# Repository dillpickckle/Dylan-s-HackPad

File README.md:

# Dylan-s-HackPad

This project is a custom 3×3 macro pad built around the Seeed XIAO RP2040, featuring a diode-protected key matrix, a rotary encoder for dynamic input, and a 128×32 SSD1306 OLED for real-time status display (RN it displays larry the SLUG). The design uses a proper row/column matrix to prevent ghosting and is powered by QMK firmware for full remapping, layers, and encoder support. This is my first time working with KiCad, and I was excited to learn how to use it through this project. It also helped to sharpen my Fusion 360 and coding skills, and that's why I made this project. 

Schematic: 

PCB:

CAD IMAGE: 

 BOM: 
9x Cherry MX Switches

9x DSA Keycaps

4x M3x5x4 Heatset inserts

9x 1N4148 DO-35 Diodes.

1x 0.91" 128x32 OLED Display

1x EC11 Rotary Encoder

1x XIAO RP2040

1x Case (2 3d Printed parts)

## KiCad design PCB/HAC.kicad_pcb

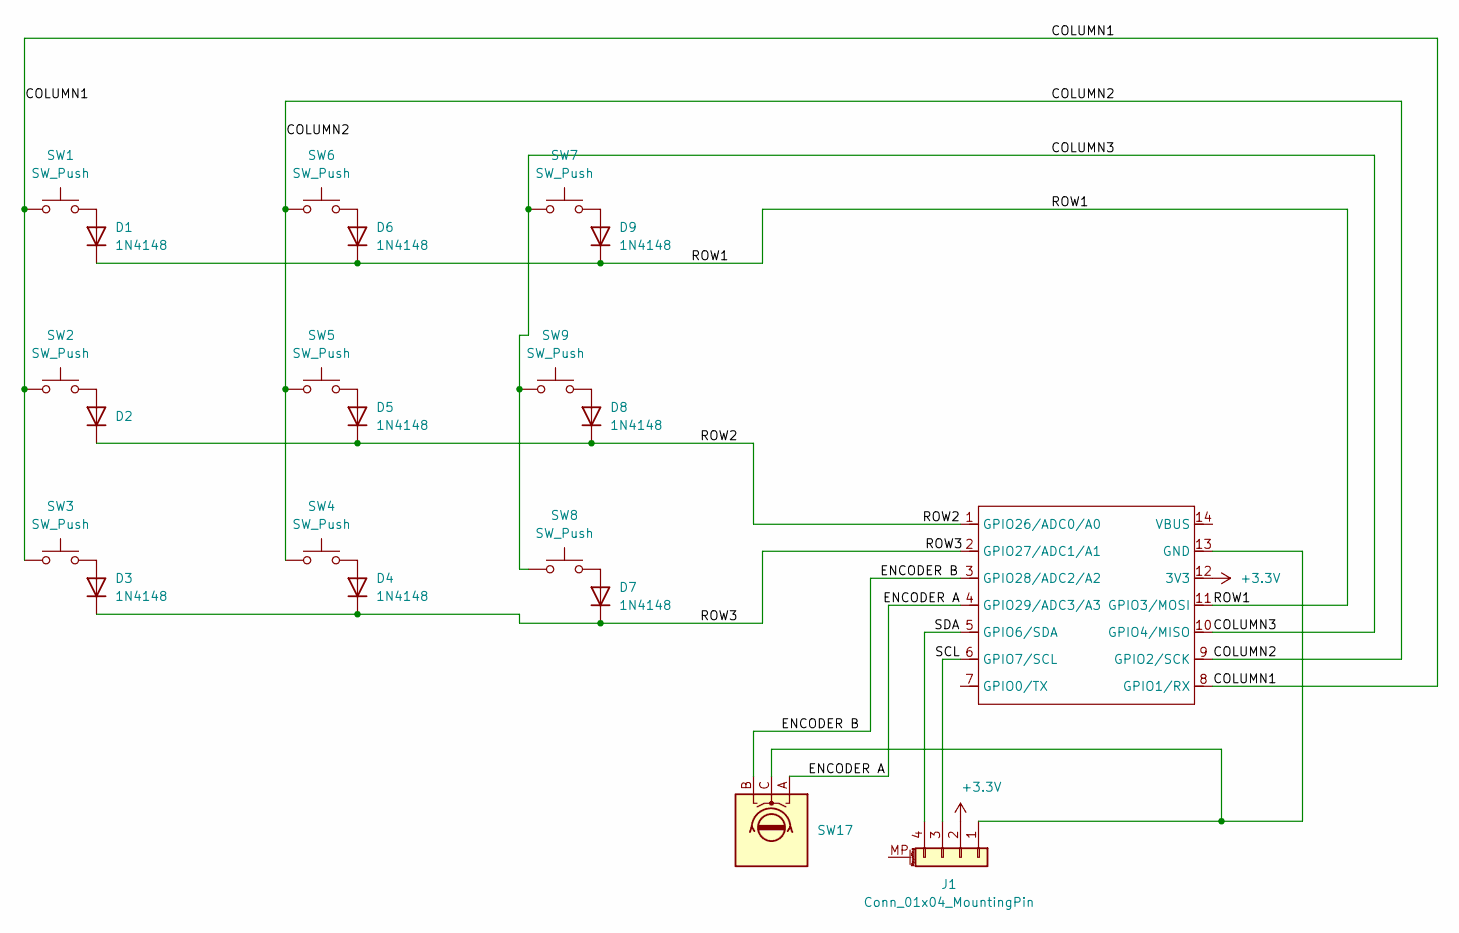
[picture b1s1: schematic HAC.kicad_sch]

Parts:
D1, D2, D3, D4, D5, D6, D7, D8, D9: 1N4148; D_DO-35_SOD27_P7.62mm_Horizontal
J1: Conn_01x04_MountingPin; SSD1306-0.91-OLED-4pin-128x32 (1)
SW1, SW2, SW3, SW4, SW5, SW6, SW7, SW8, SW9: SW_Push; SW_Cherry_MX_1.00u_PCB
SW17: RotaryEncoder; RotaryEncoder_Alps_EC11E_Vertical_H20mm
U1: XIAO-RP2040-DIP

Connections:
+3.3V: J1.2 (VCC), U1.12 (3V3)
/COLUMN1: SW1.1, SW2.1, SW3.1, U1.8 (GPIO1/RX)
/COLUMN2: SW4.1, SW5.1, SW6.1, U1.9 (GPIO2/SCK)
/COLUMN3: SW7.1, SW8.1, SW9.1, U1.10 (GPIO4/MISO)
/ENCODER A: SW17.A, U1.4 (GPIO29/ADC3/A3)
/ENCODER B: SW17.B, U1.3 (GPIO28/ADC2/A2)
/ROW1: D1.1 (K), D6.1 (K), D9.1 (K), U1.11 (GPIO3/MOSI)
/ROW2: D2.1 (K), D5.1 (K), D8.1 (K), U1.1 (GPIO26/ADC0/A0)
/ROW3: D3.1 (K), D4.1 (K), D7.1 (K), U1.2 (GPIO27/ADC1/A1)
/SCL: J1.3 (SCL), U1.6 (GPIO7/SCL)
/SDA: J1.4 (SDA), U1.5 (GPIO6/SDA)
unnamed: D1.2 (A), SW1.2
unnamed: D2.2 (A), SW2.2
unnamed: D3.2 (A), SW3.2
unnamed: D4.2 (A), SW4.2
unnamed: D5.2 (A), SW5.2
unnamed: D6.2 (A), SW6.2
unnamed: D7.2 (A), SW8.2
unnamed: D8.2 (A), SW9.2
unnamed: D9.2 (A), SW7.2
unnamed: J1.1 (GND), SW17.C, U1.13 (GND)

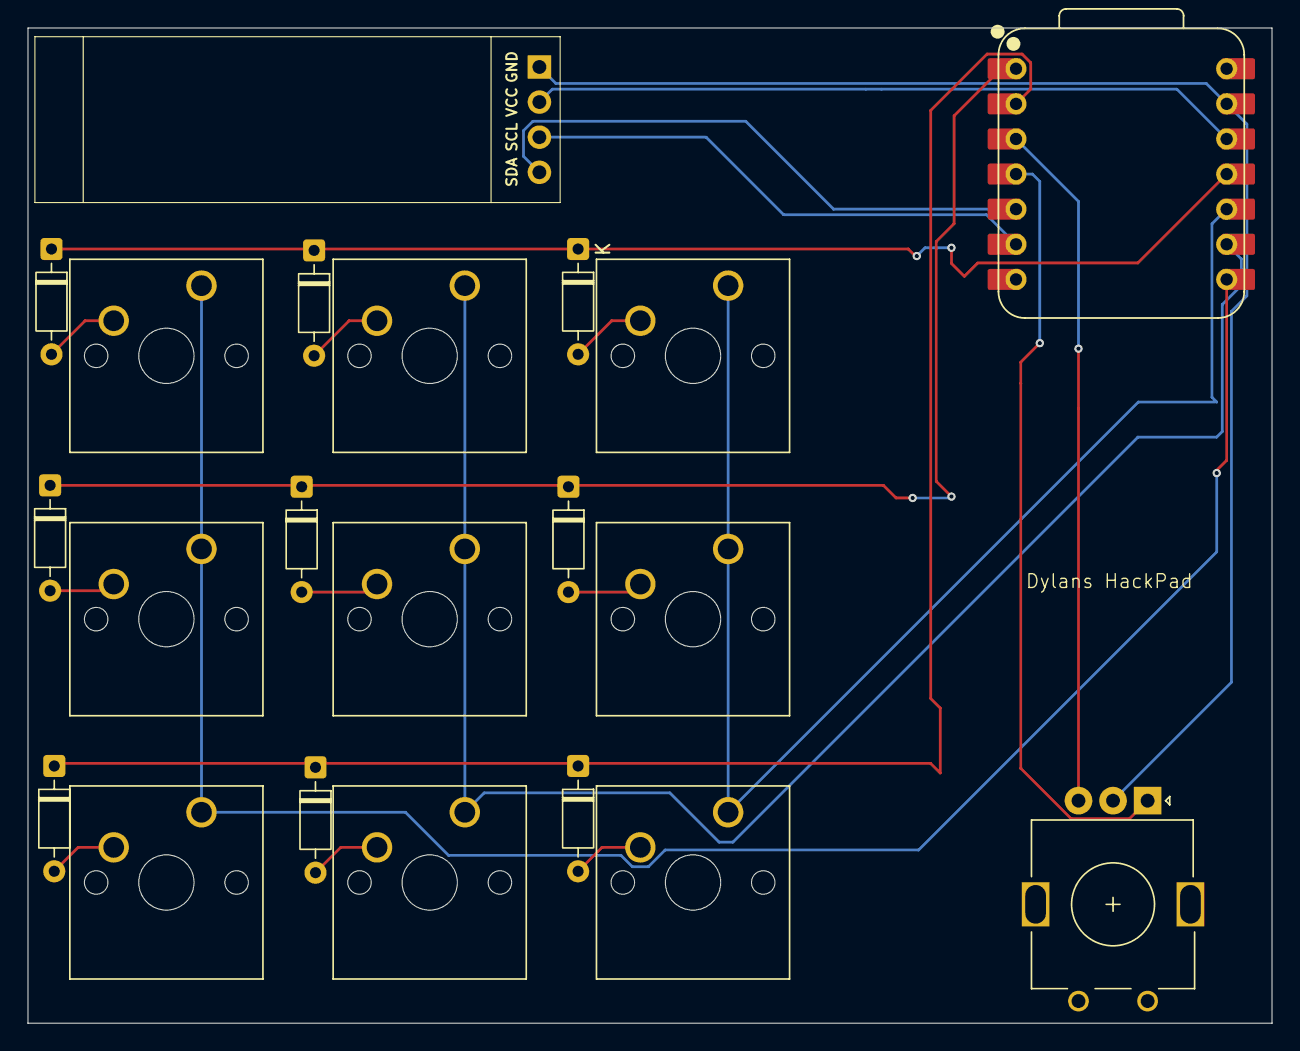
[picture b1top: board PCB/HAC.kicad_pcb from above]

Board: 2 copper layers, 90.0 x 72.0 mm, 21 parts (0 on the bottom side), 21 nets.

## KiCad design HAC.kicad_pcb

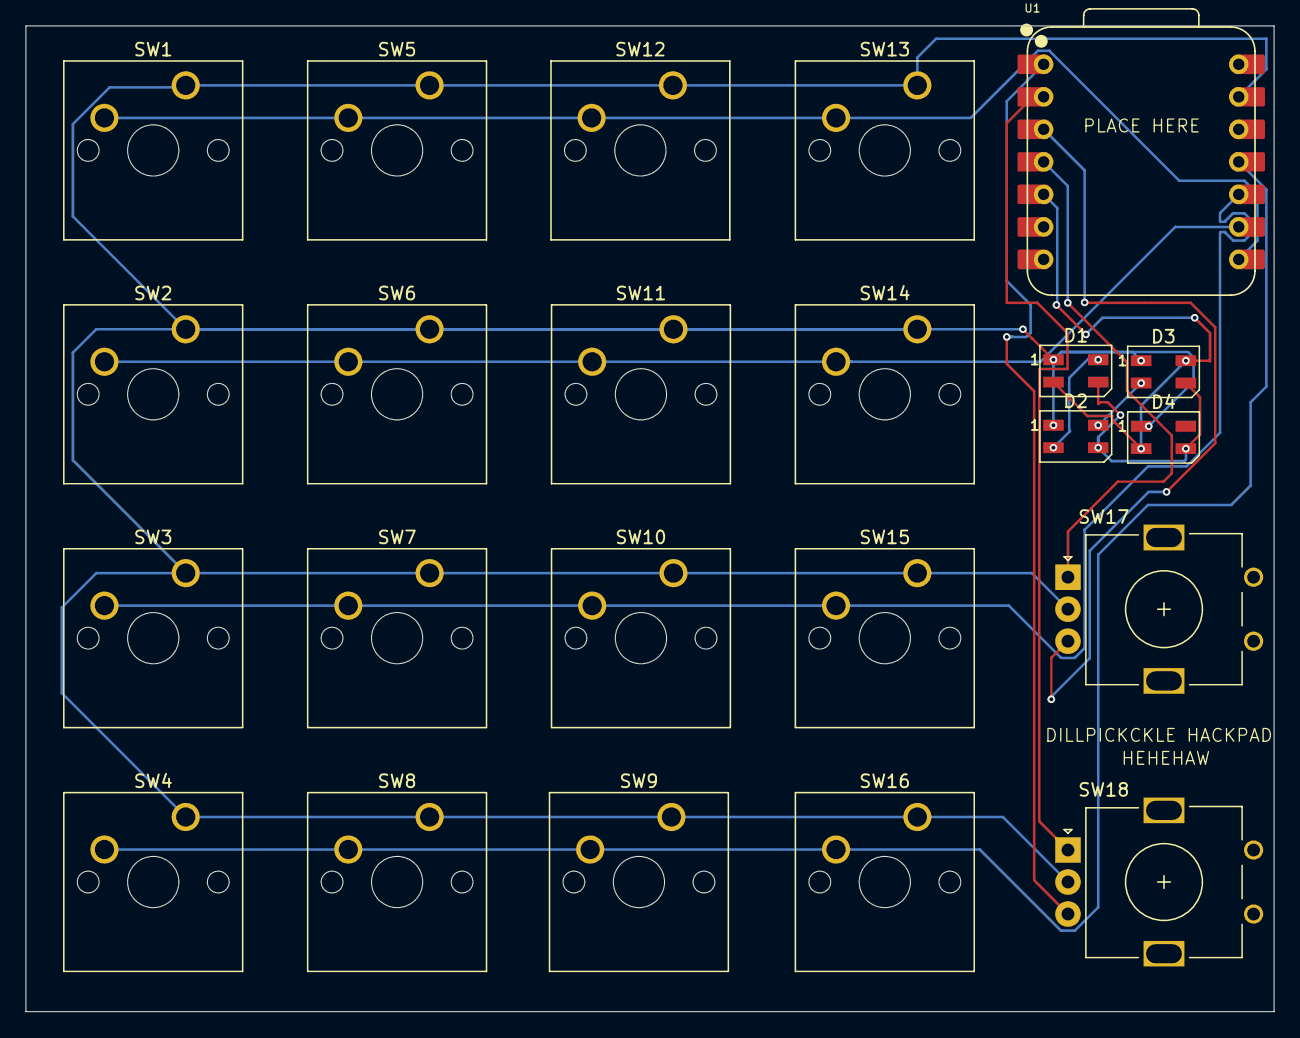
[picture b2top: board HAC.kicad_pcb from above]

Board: 2 copper layers, 97.5 x 77.0 mm, 23 parts (0 on the bottom side), 13 nets.

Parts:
D1, D2, D3, D4: SK6812; LED_SK6812MINI_PLCC4_3.5x3.5mm_P1.75mm
SW1, SW2, SW3, SW4, SW5, SW6, SW7, SW8, SW9, SW10, SW11, SW12, SW13, SW14, SW15, SW16: SW_Push; SW_Cherry_MX_1.00u_PCB
SW17, SW18: RotaryEncoder; RotaryEncoder_Alps_EC11E_Vertical_H20mm
U1: XIAO-RP2040-DIP

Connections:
+5V: D1.3 (VDD), D2.3 (VDD), D3.3 (VDD), D4.3 (VDD)
GND: D1.1 (VSS), D2.1 (VSS), D3.1 (VSS), D4.1 (VSS), SW1.1, SW2.1, SW3.1, SW4.1, SW5.1, SW6.1, SW7.1, SW8.1, SW9.1, SW10.1, SW11.1, SW12.1, SW13.1, SW14.1, SW15.1, SW16.1, SW17.C, SW18.C, U1.13 (GND)
unnamed: D1.2 (DIN), D3.4 (DOUT), D4.2 (DIN), U1.5 (GPIO6/SDA)
unnamed: D1.4 (DOUT), D2.2 (DIN)
unnamed: D2.4 (DOUT), D3.2 (DIN)
unnamed: SW1.2, SW5.2, SW12.2, SW13.2, U1.8 (GPIO1/RX)
unnamed: SW2.2, SW6.2, SW11.2, SW14.2, U1.9 (GPIO2/SCK)
unnamed: SW4.2, SW8.2, SW9.2, SW16.2, U1.11 (GPIO3/MOSI)
unnamed: SW3.2, SW7.2, SW10.2, SW15.2, U1.10 (GPIO4/MISO)
unnamed: SW18.B, U1.1 (GPIO26/ADC0/A0)
unnamed: SW18.A, U1.2 (GPIO27/ADC1/A1)
unnamed: SW17.B, U1.3 (GPIO28/ADC2/A2)
unnamed: SW17.A, U1.4 (GPIO29/ADC3/A3)

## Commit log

2026-01-11 Create CAD
2026-01-15 Create PCB
2026-01-15 Create g
2026-01-15 Create d
2026-01-17 Create e
